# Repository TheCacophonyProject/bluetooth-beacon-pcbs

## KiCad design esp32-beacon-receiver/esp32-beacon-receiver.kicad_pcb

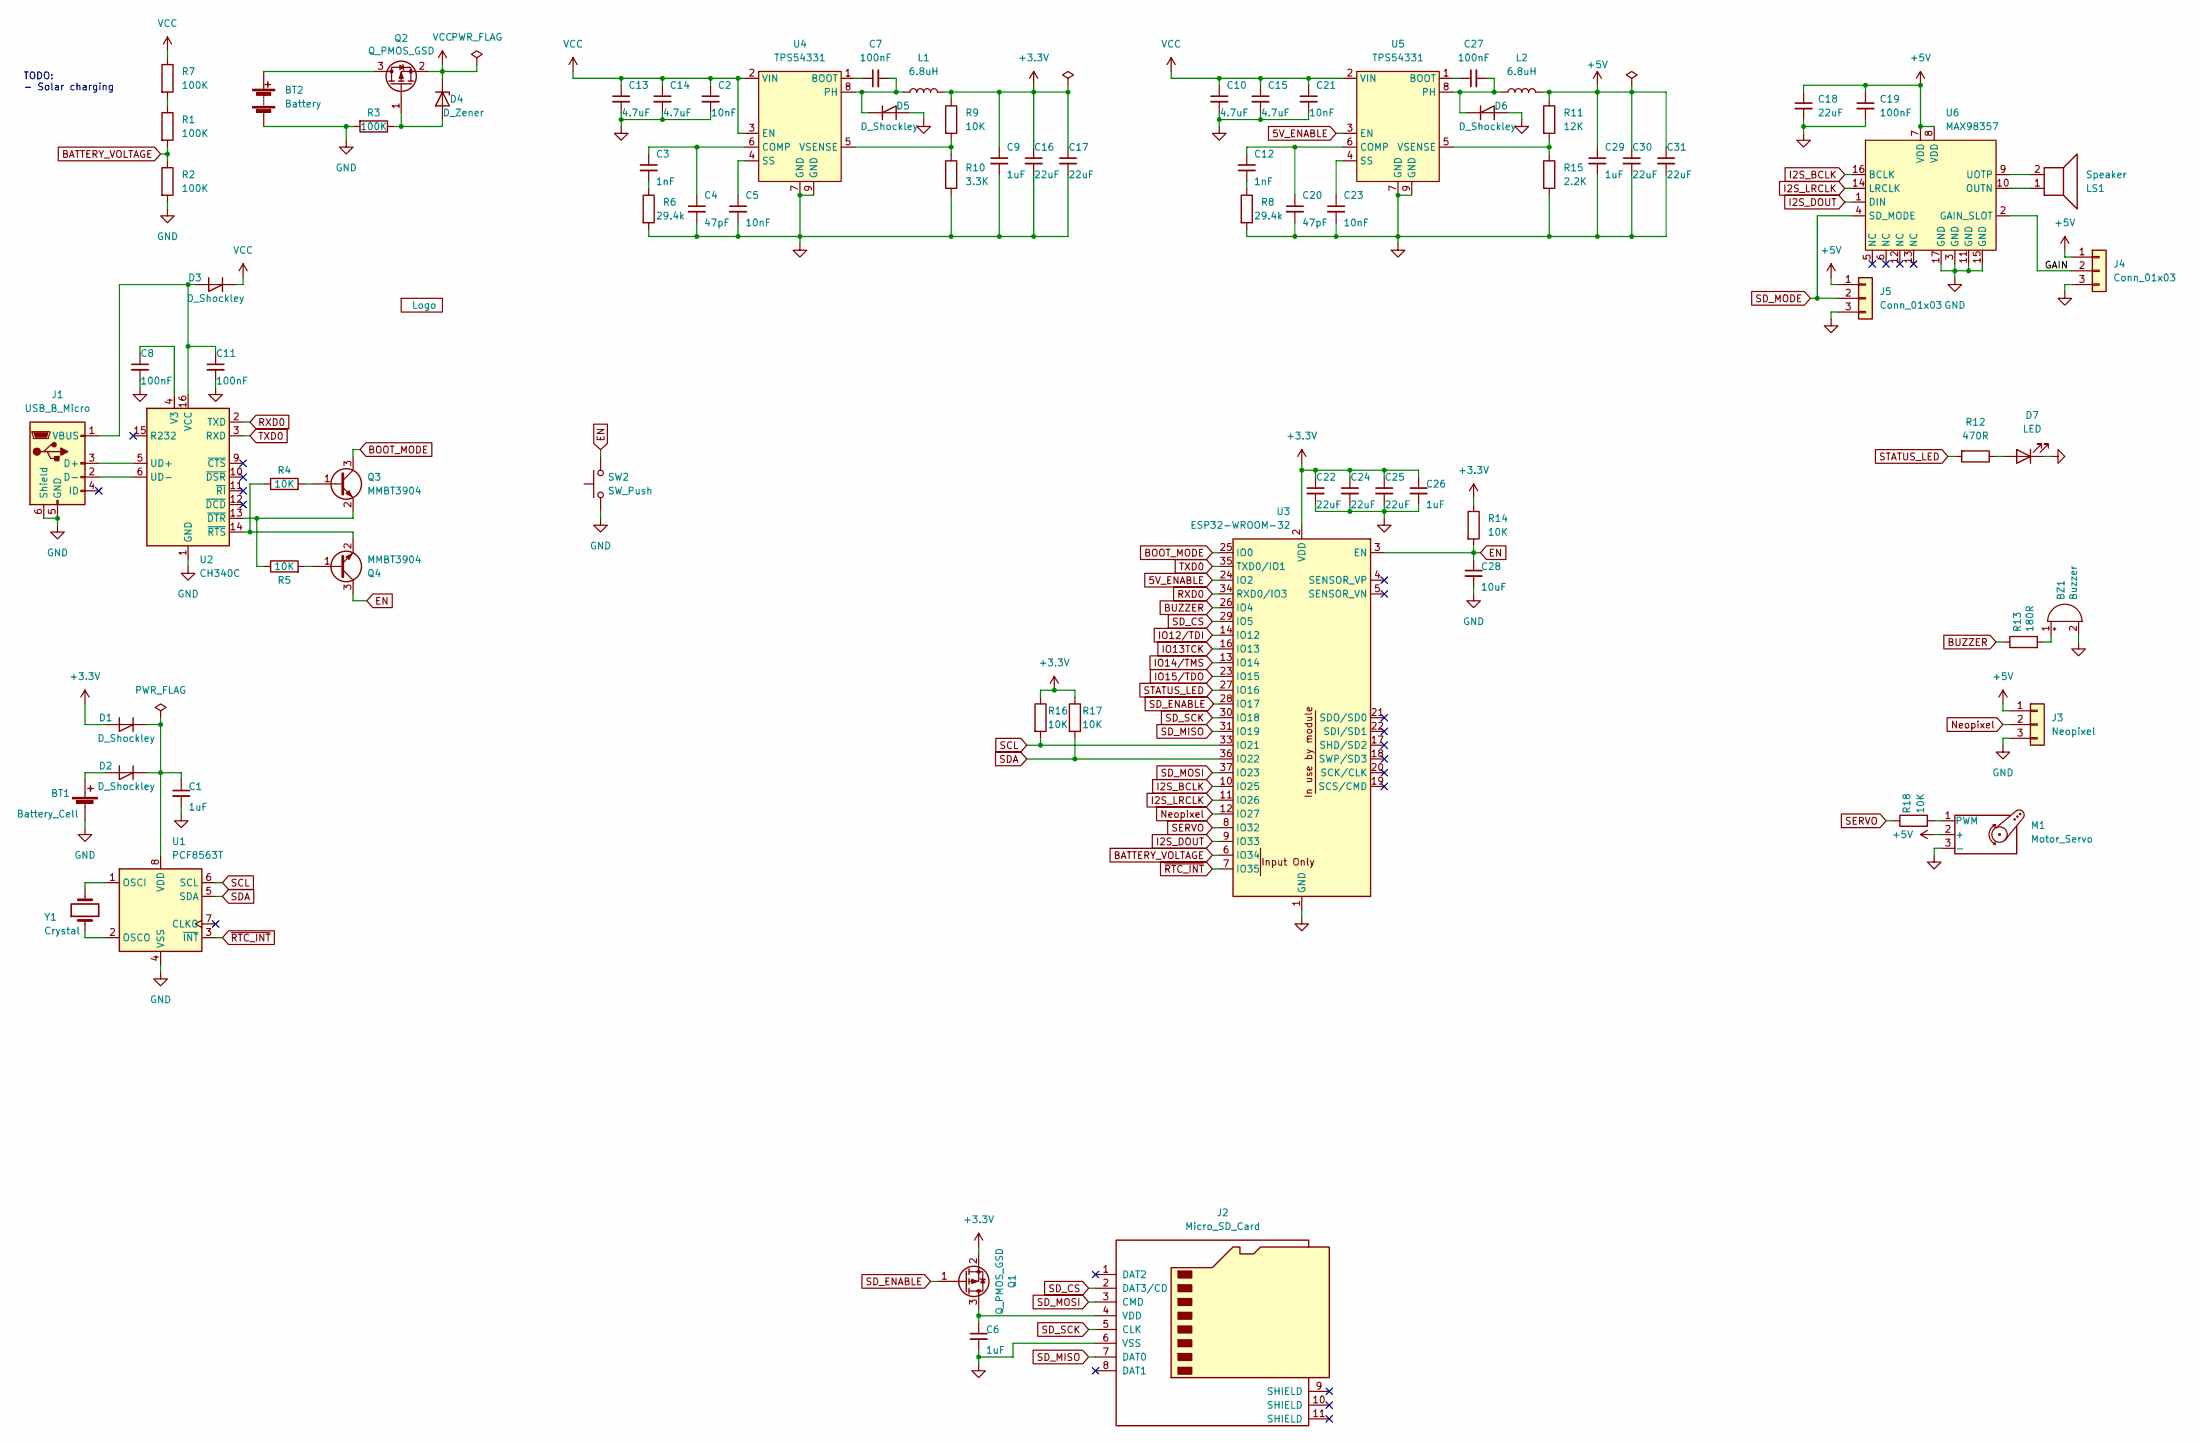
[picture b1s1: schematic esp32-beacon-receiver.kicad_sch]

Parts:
BT1: Battery_Cell; CR1220; LCSC C969906
BT2: Battery; PinSocket_1x02_P2.54mm_Vertical
BZ1: Buzzer; Buzzer_12x9.5RM7.6; LCSC C482357
C1, C6, C9, C26, C29: 1uF; C_0402_1005Metric; LCSC C52923
C2, C5, C21, C23: 10nF; C_0402_1005Metric; LCSC C15195
C3, C12: 1nF; C_0402_1005Metric; LCSC C1523
C4, C20: 47pF; C_0402_1005Metric; LCSC C1567
C7, C8, C11, C19, C27: 100nF; C_0402_1005Metric; LCSC C307331
C10, C13, C14, C15: 4.7uF; C_0402_1005Metric; LCSC C23733
C16, C17, C18, C22, C24, C25, C30, C31: 22uF; C_0805_2012Metric; LCSC C45783
C28: 10uF; C_0603_1608Metric; LCSC C19702
D1, D2, D3: D_Shockley; D_SOD-323; LCSC C191023
D4: D_Zener; D_SMA; LCSC C8062
D5, D6: D_Shockley; D_SMA; LCSC C22452
D7: LED; LED_0603_1608Metric; LCSC C2286
J1: USB_B_Micro; 920-E52A2021S10100; LCSC C10418
J2: Micro_SD_Card; SD_Micro; LCSC C585350
J3: Neopixel; PinSocket_1x03_P2.54mm_Vertical
J4, J5: Conn_01x03; PinSocket_1x03_P2.54mm_Vertical
L1, L2: 6.8uH; SWPA5040S; LCSC C36411
LS1: Speaker; PinSocket_1x02_P2.54mm_Vertical
M1: Motor_Servo; PinSocket_1x03_P2.54mm_Vertical
Q1, Q2: Q_PMOS_GSD; SOT-23; LCSC C15127
Q3, Q4: MMBT3904; SOT-23; LCSC C20526
R1, R2, R3, R7: 100K; R_0402_1005Metric; LCSC C25741
R4, R5, R9, R14, R16, R17, R18: 10K; R_0402_1005Metric; LCSC C25744
R6, R8: 29.4k; R_0402_1005Metric; LCSC C25890
R10: 3.3K; R_0402_1005Metric; LCSC C11457
R11: 12K; R_0402_1005Metric; LCSC C25744
R12: 470R; R_0402_1005Metric; LCSC C25117
R13: 180R; R_0603_1608Metric; LCSC C22828
R15: 2.2K; R_0402_1005Metric; LCSC C11457
SW2: SW_Push; SW_SPST_SKQG_WithStem; LCSC C318884
U1: PCF8563T; SOIC-8_3.9x4.9mm_P1.27mm; LCSC C7440
U2: CH340C; SOIC-16_3.9x9.9mm_P1.27mm; LCSC C84681
U3: ESP32-WROOM-32; JLCPCB C701343
U4, U5: TPS54331; SOIC-8-1EP_3.9x4.9mm_P1.27mm_EP2.29x3mm; LCSC C9865
U6: MAX98357; TQFN-16-1EP_3x3mm_P0.5mm_EP1.23x1.23mm; LCSC C910544
U7: Logo; logo
Y1: Crystal; Crystal_SMD_3215-2Pin_3.2x1.5mm; LCSC C32346

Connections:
5V_ENABLE: U3.24 (IO2), U5.3 (EN)
+3V3: C9.1, C16.1, C17.1, C22.1, C24.1, C25.1, C26.1, D1.2 (A), L1.2, Q1.2 (S), R9.1, R14.1, R16.1, R17.1, U3.2 (VDD)
+5V: C18.1, C19.1, C29.1, C30.1, C31.1, J3.1, J4.1, J5.1, L2.2, M1.2 (+), R11.1, U6.7 (VDD), U6.8 (VDD)
/GAIN: J4.2, U6.2 (GAIN_SLOT)
BATTERY_VOLTAGE: R1.2, R2.1, U3.6 (IO34)
BOOT_MODE: Q3.3 (C), U3.25 (IO0)
BUZZER: R13.1, U3.26 (IO4)
EN: C28.1, Q4.3 (C), R14.2, SW2.2, U3.3 (EN)
GND: BT1.2 (-), BT2.2 (-), BZ1.2 (+), C1.2, C2.2, C4.2, C5.2, C6.2, C8.2, C9.2, C10.2, C11.2, C13.2, C14.2, C15.2, C16.2, C17.2, C18.2, C19.2, C20.2, C21.2, C22.2, C23.2, C24.2, C25.2, C26.2, C28.2, C29.2, C30.2, C31.2, D5.2 (A), D6.2 (A), D7.1 (K), J1.5 (GND), J1.6 (Shield), J2.6 (VSS), J3.3, J4.3, J5.3, M1.3 (-), R2.2, R3.2, R6.2, R8.2, R10.2, R15.2, SW2.1, U1.4 (VSS), U2.1 (GND), U3.1 (GND), U3.15 (GND), U3.38 (GND), U3.39 (GND), U4.7 (GND), U4.9 (GND), U5.7 (GND), U5.9 (GND), U6.3 (GND), U6.11 (GND), U6.15 (GND), U6.17 (GND)
I2S_BCLK: U3.10 (IO25), U6.16 (BCLK)
I2S_DOUT: U3.9 (IO33), U6.1 (DIN)
I2S_LRCLK: U3.11 (IO26), U6.14 (LRCLK)
IO12/TDI: U3.14 (IO12)
IO13TCK: U3.16 (IO13)
IO14/TMS: U3.13 (IO14)
IO15/TDO: U3.23 (IO15)
Neopixel: J3.2, U3.12 (IO27)
unnamed: BT1.1 (+), D2.2 (A)
unnamed: BT2.1 (+), Q2.3 (D)
unnamed: BZ1.1 (-), R13.2
unnamed: C1.1, D1.1 (K), D2.1 (K), U1.8 (VDD)
unnamed: C3.1, C4.1, U4.6 (COMP)
unnamed: C3.2, R6.1
unnamed: C5.1, U4.4 (SS)
unnamed: C6.1, J2.4 (VDD), Q1.3 (D)
unnamed: C7.1, U4.1 (BOOT)
unnamed: C7.2, D5.1 (K), L1.1, U4.8 (PH)
unnamed: C8.1, U2.4 (V3)
unnamed: C11.1, D3.2 (A), J1.1 (VBUS), U2.16 (VCC)
unnamed: C12.1, C20.1, U5.6 (COMP)
unnamed: C12.2, R8.1
unnamed: C23.1, U5.4 (SS)
unnamed: C27.1, U5.1 (BOOT)
unnamed: C27.2, D6.1 (K), L2.1, U5.8 (PH)
unnamed: D4.2 (A), Q2.1 (G), R3.1
unnamed: D7.2 (A), R12.1
unnamed: J1.2 (D-), U2.6 (UD-)
unnamed: J1.3 (D+), U2.5 (UD+)
unnamed: LS1.1, U6.10 (OUTN)
unnamed: LS1.2, U6.9 (UOTP)
unnamed: M1.1 (PWM), R18.2
unnamed: Q3.1 (B), R4.2
unnamed: Q3.2 (E), R5.1, U2.13 (~DTR)
unnamed: Q4.1 (B), R5.2
unnamed: Q4.2 (E), R4.1, U2.14 (~RTS)
unnamed: R1.1, R7.2
unnamed: R9.2, R10.1, U4.5 (VSENSE)
unnamed: R11.2, R15.1, U5.5 (VSENSE)
unnamed: U1.1 (OSCI), Y1.2
unnamed: U1.2 (OSCO), Y1.1
RXD0: U2.2 (TXD), U3.34 (RXD0/IO3)
SCL: R16.2, U1.6 (SCL), U3.33 (IO21)
SDA: R17.2, U1.5 (SDA), U3.36 (IO22)
SD_CS: J2.2 (DAT3/CD), U3.29 (IO5)
SD_ENABLE: Q1.1 (G), U3.28 (IO17)
SD_MISO: J2.7 (DAT0), U3.31 (IO19)
SD_MODE: J5.2, U6.4 (SD_MODE)
SD_MOSI: J2.3 (CMD), U3.37 (IO23)
SD_SCK: J2.5 (CLK), U3.30 (IO18)
SERVO: R18.1, U3.8 (IO32)
STATUS_LED: R12.2, U3.27 (IO16)
TXD0: U2.3 (RXD), U3.35 (TXD0/IO1)
VCC: C2.1, C10.1, C13.1, C14.1, C15.1, C21.1, D3.1 (K), D4.1 (K), Q2.2 (S), R7.1, U4.2 (VIN), U4.3 (EN), U5.2 (VIN)
~RTC_INT: U1.3 (~INT), U3.7 (IO35)

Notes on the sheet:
TODO: - Solar charging

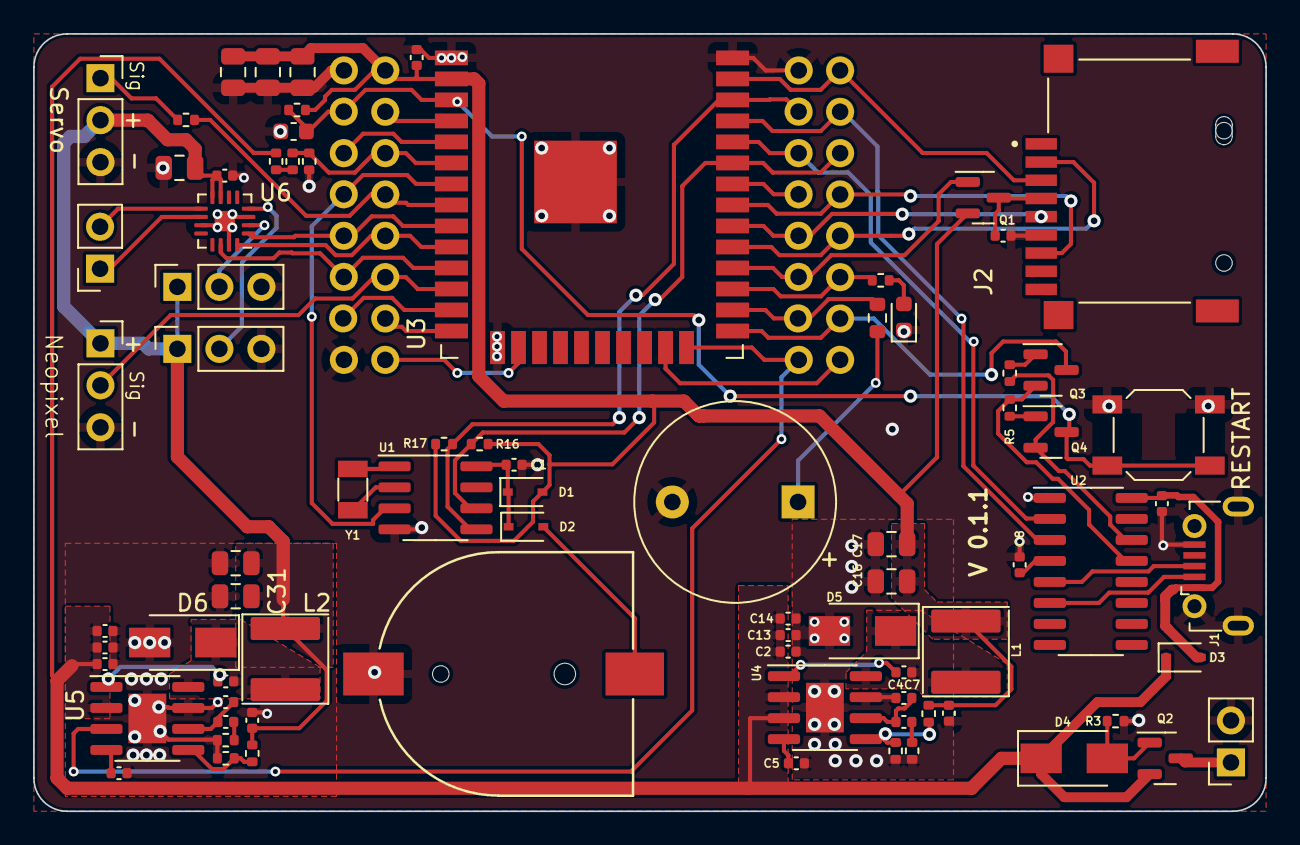
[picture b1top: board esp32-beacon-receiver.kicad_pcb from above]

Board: 2 copper layers, 74.5 x 47.0 mm, 81 parts (1 on the bottom side), 60 nets.

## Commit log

2022-03-24 Fixed some things
